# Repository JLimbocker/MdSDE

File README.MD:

###MdSDE###
This repository contains the Board files and Software for the SMU MdSDE Universal Biasing Board Project

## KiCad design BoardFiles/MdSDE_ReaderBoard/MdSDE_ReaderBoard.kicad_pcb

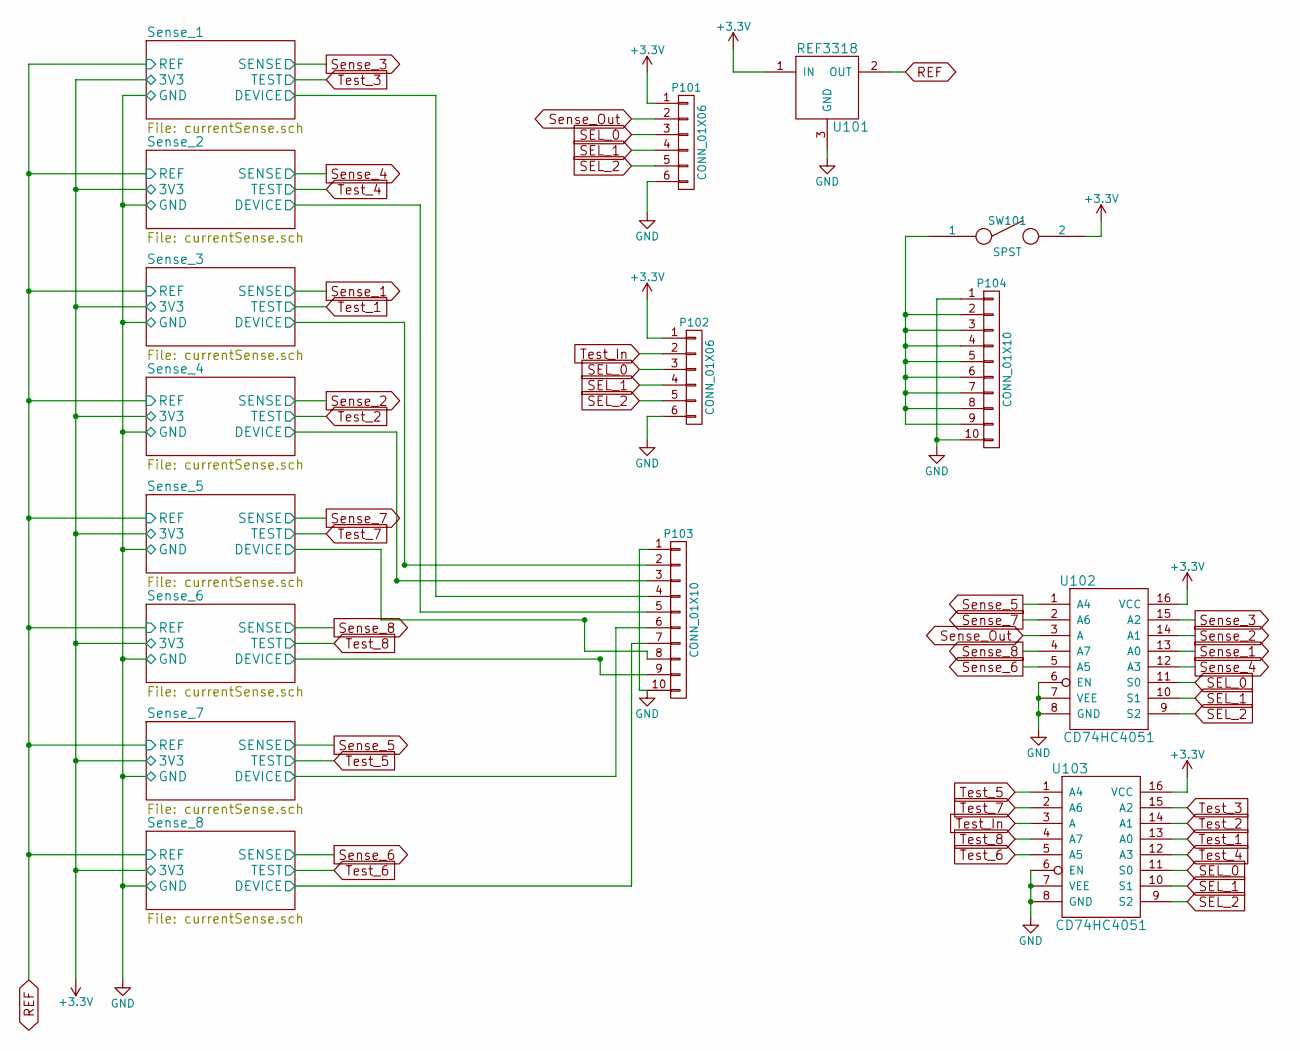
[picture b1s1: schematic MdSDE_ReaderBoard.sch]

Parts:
P101, P102: CONN_01X06; Pin_Header_Straight_1x06
P103, P104: CONN_01X10; Pin_Header_Straight_1x10
SW101: SPST; SW_DIP_x1_Slide
U101: REF3318; SOT-23_Handsoldering
U102, U103: CD74HC4051; SOIC-16_3.9x9.9mm_Pitch1.27mm

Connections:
+3V3: P101.1, P102.1, SW101.2, U101.1 (IN), U102.16 (VCC), U103.16 (VCC); also elsewhere on the board
/Sense_1/DEVICE: P103.4; also elsewhere on the board
/Sense_2/DEVICE: P103.5; also elsewhere on the board
/Sense_3/DEVICE: P103.2; also elsewhere on the board
/Sense_4/DEVICE: P103.3; also elsewhere on the board
/Sense_5/DEVICE: P103.8; also elsewhere on the board
/Sense_6/DEVICE: P103.9; also elsewhere on the board
/Sense_7/DEVICE: P103.6; also elsewhere on the board
/Sense_8/DEVICE: P103.7; also elsewhere on the board
GND: P101.6, P102.6, P103.1, P103.10, P104.1, P104.10, U101.3 (GND), U102.6 (EN), U102.7 (VEE), U102.8 (GND), U103.6 (EN), U103.7 (VEE), U103.8 (GND); also elsewhere on the board
unnamed: P104.2, P104.3, P104.4, P104.5, P104.6, P104.7, P104.8, P104.9, SW101.1
REF: U101.2 (OUT); also elsewhere on the board
SEL_0: P101.3, P102.3, U102.11 (S0), U103.11 (S0)
SEL_1: P101.4, P102.4, U102.10 (S1), U103.10 (S1)
SEL_2: P101.5, P102.5, U102.9 (S2), U103.9 (S2)
Sense_1: U102.13 (A0); also elsewhere on the board
Sense_2: U102.14 (A1); also elsewhere on the board
Sense_3: U102.15 (A2); also elsewhere on the board
Sense_4: U102.12 (A3); also elsewhere on the board
Sense_5: U102.1 (A4); also elsewhere on the board
Sense_6: U102.5 (A5); also elsewhere on the board
Sense_7: U102.2 (A6); also elsewhere on the board
Sense_8: U102.4 (A7); also elsewhere on the board
Sense_Out: P101.2, U102.3 (A)
Test_1: U103.13 (A0); also elsewhere on the board
Test_2: U103.14 (A1); also elsewhere on the board
Test_3: U103.15 (A2); also elsewhere on the board
Test_4: U103.12 (A3); also elsewhere on the board
Test_5: U103.1 (A4); also elsewhere on the board
Test_6: U103.5 (A5); also elsewhere on the board
Test_7: U103.2 (A6); also elsewhere on the board
Test_8: U103.4 (A7); also elsewhere on the board
Test_In: P102.2, U103.3 (A)

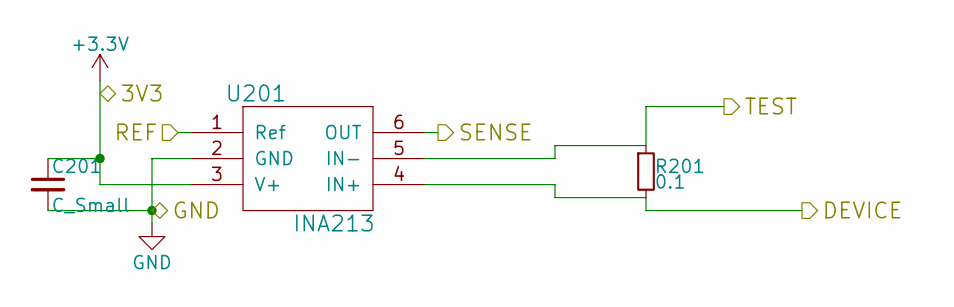
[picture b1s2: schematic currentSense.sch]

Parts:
C201: C_Small; C_1206_HandSoldering
R201: 0.1; R_1206_HandSoldering
U201: INA213; SC-70-6_Handsoldering

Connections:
+3V3: C201.1, U201.3 (V+); also elsewhere on the board
/Sense_3/DEVICE: R201.2, U201.4 (IN+); also elsewhere on the board
GND: C201.2, U201.2 (GND); also elsewhere on the board
REF: U201.1 (Ref); also elsewhere on the board
Sense_1: U201.6 (OUT); also elsewhere on the board
Test_1: R201.1, U201.5 (IN-); also elsewhere on the board

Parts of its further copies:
C301, C401, C501, C601, C701, C801, C901: C_Small; C_1206_HandSoldering
R301, R401, R501, R601, R701, R801, R901: 0.1; R_1206_HandSoldering
U301, U401, U501, U601, U701, U801, U901: INA213; SC-70-6_Handsoldering

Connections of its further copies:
+3V3: C301.1, C401.1, C501.1, C601.1, C701.1, C801.1, C901.1, U301.3 (V+), U401.3 (V+), U501.3 (V+), U601.3 (V+), U701.3 (V+), U801.3 (V+), U901.3 (V+); also elsewhere on the board
/Sense_1/DEVICE: R401.2, U401.4 (IN+); also elsewhere on the board
/Sense_2/DEVICE: R501.2, U501.4 (IN+); also elsewhere on the board
/Sense_4/DEVICE: R301.2, U301.4 (IN+); also elsewhere on the board
/Sense_5/DEVICE: R801.2, U801.4 (IN+); also elsewhere on the board
/Sense_6/DEVICE: R901.2, U901.4 (IN+); also elsewhere on the board
/Sense_7/DEVICE: R601.2, U601.4 (IN+); also elsewhere on the board
/Sense_8/DEVICE: R701.2, U701.4 (IN+); also elsewhere on the board
GND: C301.2, C401.2, C501.2, C601.2, C701.2, C801.2, C901.2, U301.2 (GND), U401.2 (GND), U501.2 (GND), U601.2 (GND), U701.2 (GND), U801.2 (GND), U901.2 (GND); also elsewhere on the board
REF: U301.1 (Ref), U401.1 (Ref), U501.1 (Ref), U601.1 (Ref), U701.1 (Ref), U801.1 (Ref), U901.1 (Ref); also elsewhere on the board
Sense_2: U301.6 (OUT); also elsewhere on the board
Sense_3: U401.6 (OUT); also elsewhere on the board
Sense_4: U501.6 (OUT); also elsewhere on the board
Sense_5: U601.6 (OUT); also elsewhere on the board
Sense_6: U701.6 (OUT); also elsewhere on the board
Sense_7: U801.6 (OUT); also elsewhere on the board
Sense_8: U901.6 (OUT); also elsewhere on the board
Test_2: R301.1, U301.5 (IN-); also elsewhere on the board
Test_3: R401.1, U401.5 (IN-); also elsewhere on the board
Test_4: R501.1, U501.5 (IN-); also elsewhere on the board
Test_5: R601.1, U601.5 (IN-); also elsewhere on the board
Test_6: R701.1, U701.5 (IN-); also elsewhere on the board
Test_7: R801.1, U801.5 (IN-); also elsewhere on the board
Test_8: R901.1, U901.5 (IN-); also elsewhere on the board

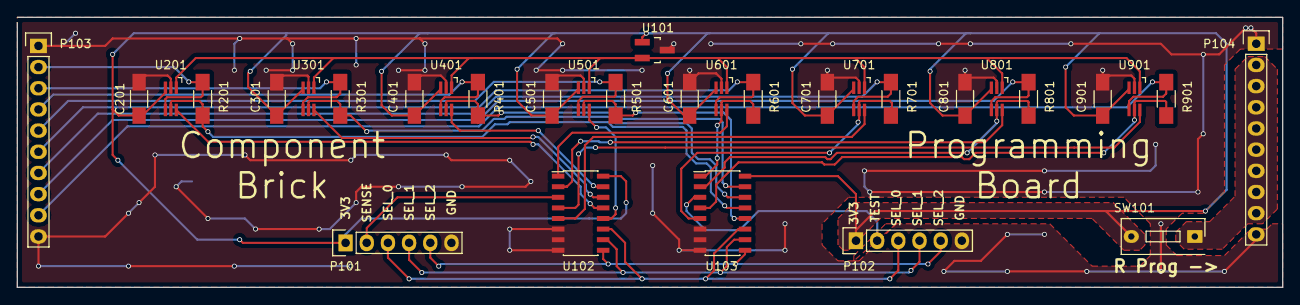
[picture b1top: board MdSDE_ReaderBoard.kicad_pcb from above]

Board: 2 copper layers, 151.8 x 32.4 mm, 32 parts (0 on the bottom side), 33 nets.

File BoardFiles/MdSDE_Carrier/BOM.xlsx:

ref | value5 | part | Quantity | Distributor | Dist Part # | MFR | MFR Part # | Price | Link
C | 10u | CP1_Small | 8 | Mouser | 140-REA470M1CBK0511P |  | REA470M1CBK-0511P | 0.06 | http://www.mouser.com/ProductDetail/Lelon/REA470M1CBK-0511P/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
C | 0.1u | C_Small | 16 | Mouser | 21RZ310-RC | Xicon | 21RZ310-RC | 0.08 | http://www.mouser.com/ProductDetail/Xicon/21RZ310-RC/?qs=sGA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
D | D | D | 16 | Mouser | 863-NSR0530HT1G | ON Semi | NSR0530HT1G | 0.14199999999999999 | http://www.mouser.com/ProductDetail/ON-Semiconductor/NSR0530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
P | 1x6 | CONN_01X06 | 8 | Mouser | 636-25630601RP2 | NorComp | 25630601RP2 | 1.83 | http://www.mouser.com/ProductDetail/NorComp/25630601RP2/?qs=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
P | 1x8 | CONN_01X08 | 4 | Mouser | 651-1789472 | Phoenix Contact | 1789472 | 8.48 | http://www.mouser.com/ProductDetail/Phoenix-Contact/1789472/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
P | 1x3 | CONN_01X03 | 1 | Mouser | 571-2828343 | TE Connectivity | 282834-3 | 1.51 | http://www.mouser.com/ProductDetail/TE-Connectivity/282834-3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
P | 2x7 | Socket_DIP14 | 16 | Mouser | 855-M22-7130742 | Harwin | M22-7130742 | 1.05 | http://www.mouser.com/ProductDetail/Harwin/M22-7130742/?qs=s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
R | 0.1 | R_Small | 16 | Mouser | 667-ERJ-8BWFR100V | Panasonic | ERJ-8BWFR100V | 1.17 | http://www.mouser.com/ProductDetail/Panasonic/ERJ-8BWFR100V/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
R | 2k | R_Small | 16 | Mouser | 660-RK73H2BTTD2001F | KOA Speer | RK73H2BTTD2001F | 0.1 | http://www.mouser.com/ProductDetail/KOA-Speer/RK73H2BTTD2001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
U | REF3318 | REF3318 | 8 | Mouser | 595-REF3318AIDBZT | TI | REF3318AIDBZT | 2.65 | http://www.mouser.com/search/ProductDetail.aspx?qs=7KoJEllG3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
U | INA213 | INA213 | 16 | Mouser | 595-INA213BIDCKR | TI | INA213BIDCKR | 1.46 | http://www.mouser.com/ProductDetail/Texas-Instruments/INA213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

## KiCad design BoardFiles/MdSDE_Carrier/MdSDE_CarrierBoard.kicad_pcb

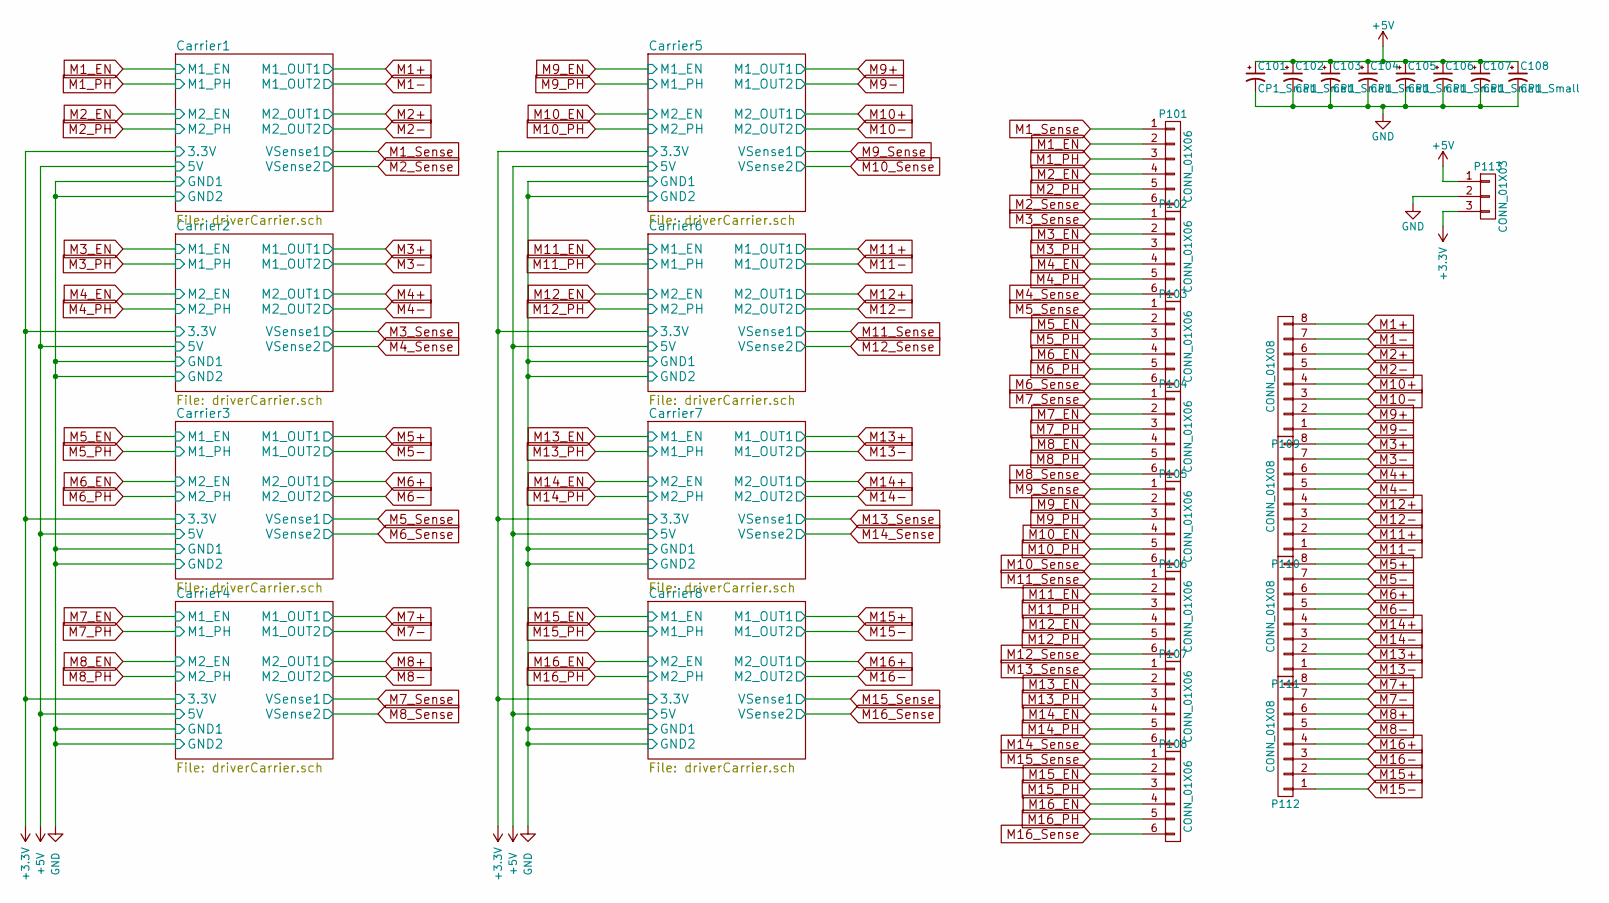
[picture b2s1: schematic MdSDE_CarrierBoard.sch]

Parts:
C101, C102, C103, C104, C105, C106, C107, C108: CP1_Small; C_Radial_D5_L6_P2.5
P101, P102, P103, P104, P105, P106, P107, P108: CONN_01X06; Pin_Header_Straight_1x06
P109, P110, P111, P112: CONN_01X08; Phoenix_FFKDS_V-25,4-8
P113: CONN_01X03; PINHEAD1-3

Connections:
+3V3: P113.3; also elsewhere on the board
+5V: C101.1, C102.1, C103.1, C104.1, C105.1, C106.1, C107.1, C108.1, P113.1; also elsewhere on the board
GND: C101.2, C102.2, C103.2, C104.2, C105.2, C106.2, C107.2, C108.2, P113.2; also elsewhere on the board
M1+: P109.8; also elsewhere on the board
M1-: P109.7; also elsewhere on the board
M1_EN: P101.2; also elsewhere on the board
M1_PH: P101.3; also elsewhere on the board
M1_Sense: P101.1; also elsewhere on the board
M2+: P109.6; also elsewhere on the board
M2-: P109.5; also elsewhere on the board
M2_EN: P101.4; also elsewhere on the board
M2_PH: P101.5; also elsewhere on the board
M2_Sense: P101.6; also elsewhere on the board
M3+: P110.8; also elsewhere on the board
M3-: P110.7; also elsewhere on the board
M3_EN: P102.2; also elsewhere on the board
M3_PH: P102.3; also elsewhere on the board
M3_Sense: P102.1; also elsewhere on the board
M4+: P110.6; also elsewhere on the board
M4-: P110.5; also elsewhere on the board
M4_EN: P102.4; also elsewhere on the board
M4_PH: P102.5; also elsewhere on the board
M4_Sense: P102.6; also elsewhere on the board
M5+: P111.8; also elsewhere on the board
M5-: P111.7; also elsewhere on the board
M5_EN: P103.2; also elsewhere on the board
M5_PH: P103.3; also elsewhere on the board
M5_Sense: P103.1; also elsewhere on the board
M6+: P111.6; also elsewhere on the board
M6-: P111.5; also elsewhere on the board
M6_EN: P103.4; also elsewhere on the board
M6_PH: P103.5; also elsewhere on the board
M6_Sense: P103.6; also elsewhere on the board
M7+: P112.8; also elsewhere on the board
M7-: P112.7; also elsewhere on the board
M7_EN: P104.2; also elsewhere on the board
M7_PH: P104.3; also elsewhere on the board
M7_Sense: P104.1; also elsewhere on the board
M8+: P112.6; also elsewhere on the board
M8-: P112.5; also elsewhere on the board
M8_EN: P104.4; also elsewhere on the board
M8_PH: P104.5; also elsewhere on the board
M8_Sense: P104.6; also elsewhere on the board
M9+: P109.2; also elsewhere on the board
M9-: P109.1; also elsewhere on the board
M9_EN: P105.2; also elsewhere on the board
M9_PH: P105.3; also elsewhere on the board
M9_Sense: P105.1; also elsewhere on the board
M10+: P109.4; also elsewhere on the board
M10-: P109.3; also elsewhere on the board
M10_EN: P105.4; also elsewhere on the board
M10_PH: P105.5; also elsewhere on the board
M10_Sense: P105.6; also elsewhere on the board
M11+: P110.2; also elsewhere on the board
M11-: P110.1; also elsewhere on the board
M11_EN: P106.2; also elsewhere on the board
M11_PH: P106.3; also elsewhere on the board
M11_Sense: P106.1; also elsewhere on the board
M12+: P110.4; also elsewhere on the board
M12-: P110.3; also elsewhere on the board
M12_EN: P106.4; also elsewhere on the board
M12_PH: P106.5; also elsewhere on the board
M12_Sense: P106.6; also elsewhere on the board
M13+: P111.2; also elsewhere on the board
M13-: P111.1; also elsewhere on the board
M13_EN: P107.2; also elsewhere on the board
M13_PH: P107.3; also elsewhere on the board
M13_Sense: P107.1; also elsewhere on the board
M14+: P111.4; also elsewhere on the board
M14-: P111.3; also elsewhere on the board
M14_EN: P107.4; also elsewhere on the board
M14_PH: P107.5; also elsewhere on the board
M14_Sense: P107.6; also elsewhere on the board
M15+: P112.2; also elsewhere on the board
M15-: P112.1; also elsewhere on the board
M15_EN: P108.2; also elsewhere on the board
M15_PH: P108.3; also elsewhere on the board
M15_Sense: P108.1; also elsewhere on the board
M16+: P112.4; also elsewhere on the board
M16-: P112.3; also elsewhere on the board
M16_EN: P108.4; also elsewhere on the board
M16_PH: P108.5; also elsewhere on the board
M16_Sense: P108.6; also elsewhere on the board

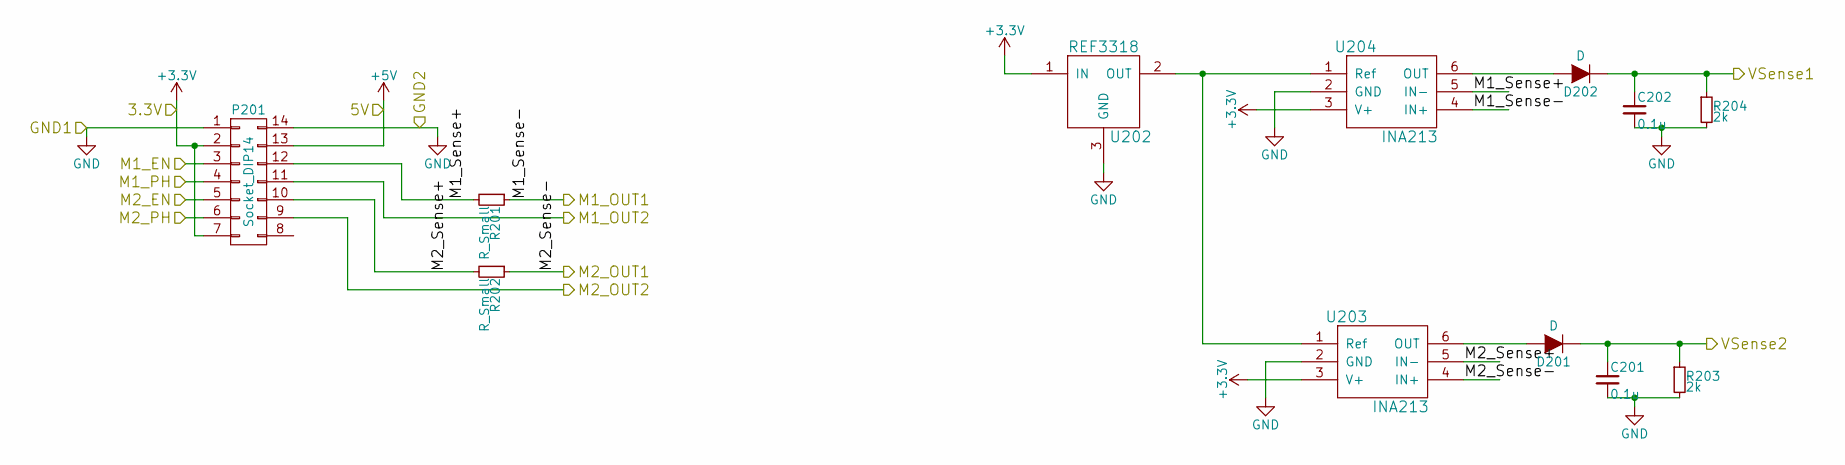
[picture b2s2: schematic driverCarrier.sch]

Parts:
C201, C202: 0.1u; C_Disc_D3_P2.5
D201, D202: D; SOD-323
P201: Socket_DIP14; DIP-14_W7.62mm
R201, R202: R_Small; R_1206_HandSoldering
R203, R204: 2k; R_1206_HandSoldering
U202: REF3318; SOT-23_Handsoldering
U203, U204: INA213; SC-70-6_Handsoldering

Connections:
+3V3: P201.2, P201.7, U202.1 (IN), U203.3 (V+), U204.3 (V+); also elsewhere on the board
+5V: P201.13; also elsewhere on the board
/Carrier1/M1_Sense+: P201.12, R201.2, U204.5 (IN-)
/Carrier1/M2_Sense+: P201.10, R202.2, U203.5 (IN-)
GND: C201.2, C202.2, P201.1, P201.14, R203.2, R204.2, U202.3 (GND), U203.2 (GND), U204.2 (GND); also elsewhere on the board
M1+: R201.1, U204.4 (IN+); also elsewhere on the board
M1-: P201.11; also elsewhere on the board
M1_EN: P201.3; also elsewhere on the board
M1_PH: P201.4; also elsewhere on the board
M1_Sense: C202.1, D202.1 (K), R204.1; also elsewhere on the board
M2+: R202.1, U203.4 (IN+); also elsewhere on the board
M2-: P201.9; also elsewhere on the board
M2_EN: P201.5; also elsewhere on the board
M2_PH: P201.6; also elsewhere on the board
M2_Sense: C201.1, D201.1 (K), R203.1; also elsewhere on the board
unnamed: D201.2 (A), U203.6 (OUT)
unnamed: D202.2 (A), U204.6 (OUT)
unnamed: U202.2 (OUT), U203.1 (Ref), U204.1 (Ref)

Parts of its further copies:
C301, C302, C401, C402, C501, C502, C601, C602, C701, C702, C801, C802, C901, C902: 0.1u; C_Disc_D3_P2.5
D301, D302, D401, D402, D501, D502, D601, D602, D701, D702, D801, D802, D901, D902: D; SOD-323
P301, P401, P501, P601, P701, P801, P901: Socket_DIP14; DIP-14_W7.62mm
R301, R302, R401, R402, R501, R502, R601, R602, R701, R702, R801, R802, R901, R902: R_Small; R_1206_HandSoldering
R303, R304, R403, R404, R503, R504, R603, R604, R703, R704, R803, R804, R903, R904: 2k; R_1206_HandSoldering
U302, U402, U502, U602, U702, U802, U902: REF3318; SOT-23_Handsoldering
U303, U304, U403, U404, U503, U504, U603, U604, U703, U704, U803, U804, U903, U904: INA213; SC-70-6_Handsoldering

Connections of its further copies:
+3V3: P301.2, P301.7, P401.2, P401.7, P501.2, P501.7, P601.2, P601.7, P701.2, P701.7, P801.2, P801.7, P901.2, P901.7, U302.1 (IN), U303.3 (V+), U304.3 (V+), U402.1 (IN), U403.3 (V+), U404.3 (V+), U502.1 (IN), U503.3 (V+), U504.3 (V+), U602.1 (IN), U603.3 (V+), U604.3 (V+), U702.1 (IN), U703.3 (V+), U704.3 (V+), U802.1 (IN), U803.3 (V+), U804.3 (V+), U902.1 (IN), U903.3 (V+), U904.3 (V+); also elsewhere on the board
+5V: P301.13, P401.13, P501.13, P601.13, P701.13, P801.13, P901.13; also elsewhere on the board
/Carrier2/M1_Sense+: P301.12, R301.2, U304.5 (IN-)
/Carrier2/M2_Sense+: P301.10, R302.2, U303.5 (IN-)
/Carrier3/M1_Sense+: P401.12, R401.2, U404.5 (IN-)
/Carrier3/M2_Sense+: P401.10, R402.2, U403.5 (IN-)
/Carrier4/M1_Sense+: P501.12, R501.2, U504.5 (IN-)
/Carrier4/M2_Sense+: P501.10, R502.2, U503.5 (IN-)
/Carrier5/M1_Sense+: P601.12, R601.2, U604.5 (IN-)
/Carrier5/M2_Sense+: P601.10, R602.2, U603.5 (IN-)
/Carrier6/M1_Sense+: P701.12, R701.2, U704.5 (IN-)
/Carrier6/M2_Sense+: P701.10, R702.2, U703.5 (IN-)
/Carrier7/M1_Sense+: P801.12, R801.2, U804.5 (IN-)
/Carrier7/M2_Sense+: P801.10, R802.2, U803.5 (IN-)
/Carrier8/M1_Sense+: P901.12, R901.2, U904.5 (IN-)
/Carrier8/M2_Sense+: P901.10, R902.2, U903.5 (IN-)
GND: C301.2, C302.2, C401.2, C402.2, C501.2, C502.2, C601.2, C602.2, C701.2, C702.2, C801.2, C802.2, C901.2, C902.2, P301.1, P301.14, P401.1, P401.14, P501.1, P501.14, P601.1, P601.14, P701.1, P701.14, P801.1, P801.14, P901.1, P901.14, R303.2, R304.2, R403.2, R404.2, R503.2, R504.2, R603.2, R604.2, R703.2, R704.2, R803.2, R804.2, R903.2, R904.2, U302.3 (GND), U303.2 (GND), U304.2 (GND), U402.3 (GND), U403.2 (GND), U404.2 (GND), U502.3 (GND), U503.2 (GND), U504.2 (GND), U602.3 (GND), U603.2 (GND), U604.2 (GND), U702.3 (GND), U703.2 (GND), U704.2 (GND), U802.3 (GND), U803.2 (GND), U804.2 (GND), U902.3 (GND), U903.2 (GND), U904.2 (GND); also elsewhere on the board
M3+: R301.1, U304.4 (IN+); also elsewhere on the board
M3-: P301.11; also elsewhere on the board
M3_EN: P301.3; also elsewhere on the board
M3_PH: P301.4; also elsewhere on the board
M3_Sense: C302.1, D302.1 (K), R304.1; also elsewhere on the board
M4+: R302.1, U303.4 (IN+); also elsewhere on the board
M4-: P301.9; also elsewhere on the board
M4_EN: P301.5; also elsewhere on the board
M4_PH: P301.6; also elsewhere on the board
M4_Sense: C301.1, D301.1 (K), R303.1; also elsewhere on the board
M5+: R401.1, U404.4 (IN+); also elsewhere on the board
M5-: P401.11; also elsewhere on the board
M5_EN: P401.3; also elsewhere on the board
M5_PH: P401.4; also elsewhere on the board
M5_Sense: C402.1, D402.1 (K), R404.1; also elsewhere on the board
M6+: R402.1, U403.4 (IN+); also elsewhere on the board
M6-: P401.9; also elsewhere on the board
M6_EN: P401.5; also elsewhere on the board
M6_PH: P401.6; also elsewhere on the board
M6_Sense: C401.1, D401.1 (K), R403.1; also elsewhere on the board
M7+: R501.1, U504.4 (IN+); also elsewhere on the board
M7-: P501.11; also elsewhere on the board
M7_EN: P501.3; also elsewhere on the board
M7_PH: P501.4; also elsewhere on the board
M7_Sense: C502.1, D502.1 (K), R504.1; also elsewhere on the board
M8+: R502.1, U503.4 (IN+); also elsewhere on the board
M8-: P501.9; also elsewhere on the board
M8_EN: P501.5; also elsewhere on the board
M8_PH: P501.6; also elsewhere on the board
M8_Sense: C501.1, D501.1 (K), R503.1; also elsewhere on the board
M9+: R601.1, U604.4 (IN+); also elsewhere on the board
M9-: P601.11; also elsewhere on the board
M9_EN: P601.3; also elsewhere on the board
M9_PH: P601.4; also elsewhere on the board
M9_Sense: C602.1, D602.1 (K), R604.1; also elsewhere on the board
M10+: R602.1, U603.4 (IN+); also elsewhere on the board
M10-: P601.9; also elsewhere on the board
M10_EN: P601.5; also elsewhere on the board
M10_PH: P601.6; also elsewhere on the board
M10_Sense: C601.1, D601.1 (K), R603.1; also elsewhere on the board
M11+: R701.1, U704.4 (IN+); also elsewhere on the board
M11-: P701.11; also elsewhere on the board
M11_EN: P701.3; also elsewhere on the board
M11_PH: P701.4; also elsewhere on the board
M11_Sense: C702.1, D702.1 (K), R704.1; also elsewhere on the board
M12+: R702.1, U703.4 (IN+); also elsewhere on the board
M12-: P701.9; also elsewhere on the board
M12_EN: P701.5; also elsewhere on the board
M12_PH: P701.6; also elsewhere on the board
M12_Sense: C701.1, D701.1 (K), R703.1; also elsewhere on the board
M13+: R801.1, U804.4 (IN+); also elsewhere on the board
M13-: P801.11; also elsewhere on the board
M13_EN: P801.3; also elsewhere on the board
M13_PH: P801.4; also elsewhere on the board
M13_Sense: C802.1, D802.1 (K), R804.1; also elsewhere on the board
M14+: R802.1, U803.4 (IN+); also elsewhere on the board
M14-: P801.9; also elsewhere on the board
M14_EN: P801.5; also elsewhere on the board
M14_PH: P801.6; also elsewhere on the board
M14_Sense: C801.1, D801.1 (K), R803.1; also elsewhere on the board
M15+: R901.1, U904.4 (IN+); also elsewhere on the board
M15-: P901.11; also elsewhere on the board
M15_EN: P901.3; also elsewhere on the board
M15_PH: P901.4; also elsewhere on the board
M15_Sense: C902.1, D902.1 (K), R904.1; also elsewhere on the board
M16+: R902.1, U903.4 (IN+); also elsewhere on the board
M16-: P901.9; also elsewhere on the board
M16_EN: P901.5; also elsewhere on the board
M16_PH: P901.6; also elsewhere on the board
M16_Sense: C901.1, D901.1 (K), R903.1; also elsewhere on the board
unnamed: D301.2 (A), U303.6 (OUT)
unnamed: D302.2 (A), U304.6 (OUT)
unnamed: D401.2 (A), U403.6 (OUT)
unnamed: D402.2 (A), U404.6 (OUT)
unnamed: D501.2 (A), U503.6 (OUT)
unnamed: D502.2 (A), U504.6 (OUT)
unnamed: D601.2 (A), U603.6 (OUT)
unnamed: D602.2 (A), U604.6 (OUT)
unnamed: D701.2 (A), U703.6 (OUT)
unnamed: D702.2 (A), U704.6 (OUT)
unnamed: D801.2 (A), U803.6 (OUT)
unnamed: D802.2 (A), U804.6 (OUT)
unnamed: D901.2 (A), U903.6 (OUT)
unnamed: D902.2 (A), U904.6 (OUT)
unnamed: U302.2 (OUT), U303.1 (Ref), U304.1 (Ref)
unnamed: U402.2 (OUT), U403.1 (Ref), U404.1 (Ref)
unnamed: U502.2 (OUT), U503.1 (Ref), U504.1 (Ref)
unnamed: U602.2 (OUT), U603.1 (Ref), U604.1 (Ref)
unnamed: U702.2 (OUT), U703.1 (Ref), U704.1 (Ref)
unnamed: U802.2 (OUT), U803.1 (Ref), U804.1 (Ref)
unnamed: U902.2 (OUT), U903.1 (Ref), U904.1 (Ref)

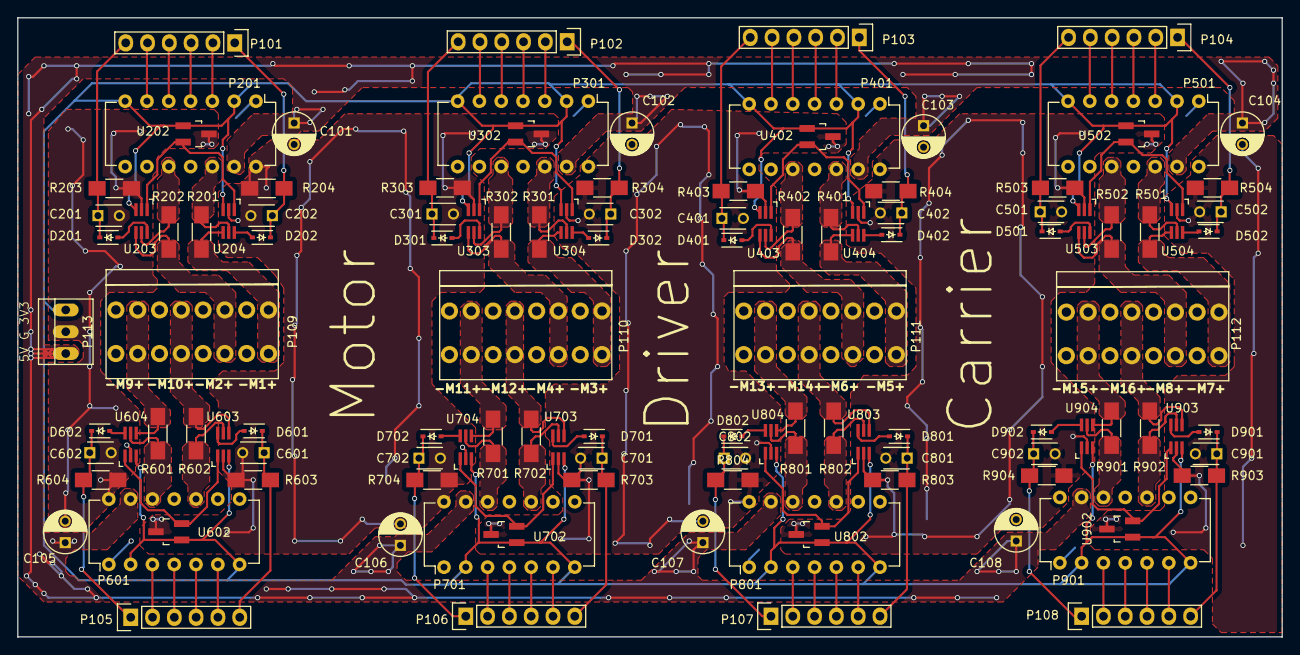
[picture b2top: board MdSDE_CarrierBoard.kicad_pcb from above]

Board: 2 copper layers, 147.3 x 72.1 mm, 117 parts (0 on the bottom side), 123 nets.

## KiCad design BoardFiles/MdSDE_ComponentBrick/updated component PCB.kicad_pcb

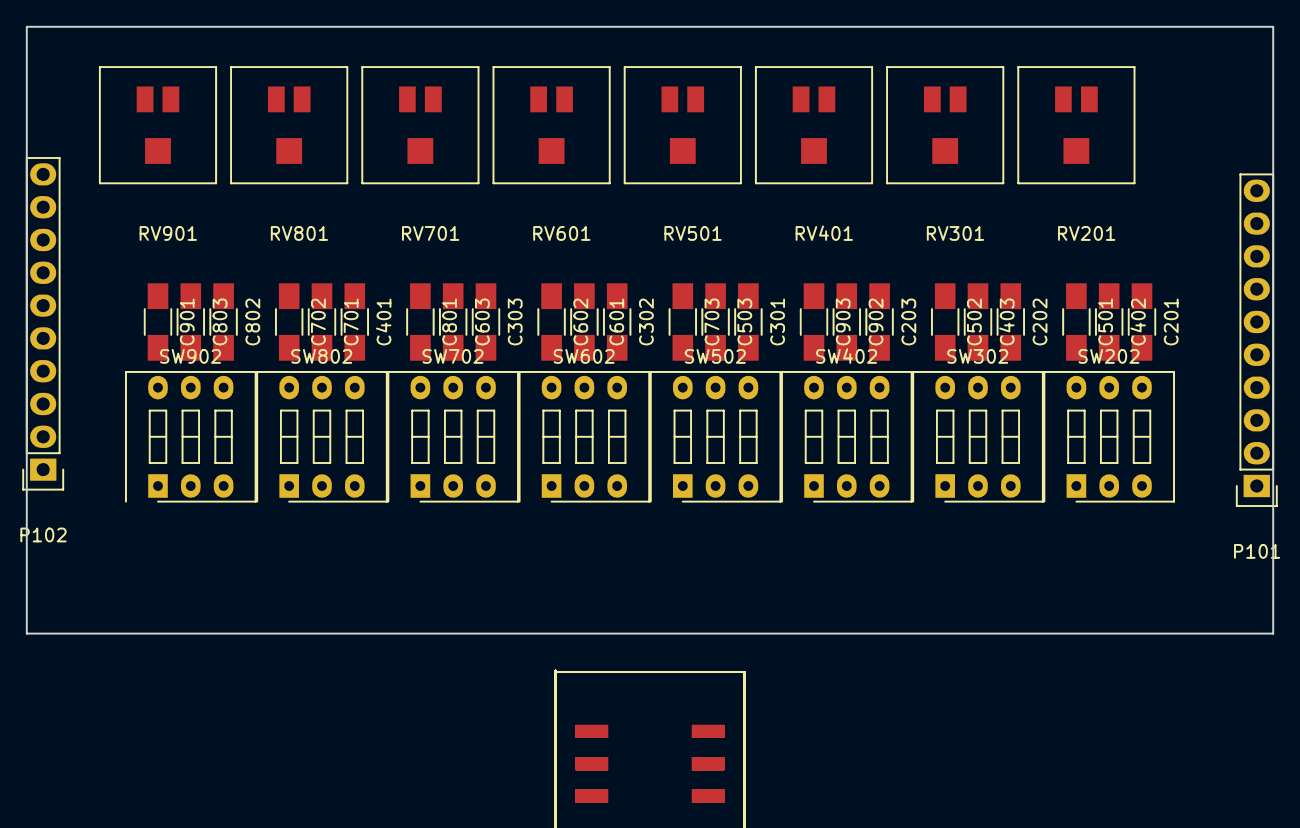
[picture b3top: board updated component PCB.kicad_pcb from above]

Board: 2 copper layers, 96.5 x 47.0 mm, 50 parts (0 on the bottom side), 57 nets, no tracks yet.

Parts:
C201, C202, C203, C301, C302, C303, C401, C402, C403, C501, C502, C503, C601, C602, C603, C701, C702, C703, C801, C802, C803, C901, C902, C903: C_Small; C_1206_HandSoldering
P101, P102: CONN_01X10; Pin_Header_Straight_1x10
RV201, RV301, RV401, RV501, RV601, RV701, RV801, RV901: POT; 3314_Potentiometer
SW201, SW301, SW401, SW501, SW601, SW701, SW801, SW901: Coded_Switch; SH-7000RotarySwitch
SW202, SW302, SW402, SW502, SW602, SW702, SW802, SW902: SPST_x3; SW_DIP_x3_Slide

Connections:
GND: C201.2, C202.2, C203.2, C301.2, C302.2, C303.2, C401.2, C402.2, C403.2, C501.2, C502.2, C503.2, C601.2, C602.2, C603.2, C701.2, C702.2, C703.2, C801.2, C802.2, C803.2, C901.2, C902.2, C903.2, P101.1, P101.10, P102.1, P102.10, SW201.5, SW202.4, SW301.5, SW302.4, SW401.5, SW402.4, SW501.5, SW502.4, SW601.5, SW602.4, SW701.5, SW702.4, SW801.5, SW802.4, SW901.5, SW902.4
unnamed: C201.1, SW201.4
unnamed: C202.1, SW201.3
unnamed: C203.1, SW201.2
unnamed: C301.1, SW301.4
unnamed: C302.1, SW301.3
unnamed: C303.1, SW301.2
unnamed: C401.1, SW401.4
unnamed: C402.1, SW401.3
unnamed: C403.1, SW401.2
unnamed: C501.1, SW501.4
unnamed: C502.1, SW501.3
unnamed: C503.1, SW501.2
unnamed: C601.1, SW601.4
unnamed: C602.1, SW601.3
unnamed: C603.1, SW601.2
unnamed: C701.1, SW701.4
unnamed: C702.1, SW701.3
unnamed: C703.1, SW701.2
unnamed: C801.1, SW801.4
unnamed: C802.1, SW801.3
unnamed: C803.1, SW801.2
unnamed: C901.1, SW901.4
unnamed: C902.1, SW901.3
unnamed: C903.1, SW901.2
unnamed: RV201.1, SW202.3
unnamed: RV201.2, SW202.2, SW202.5
unnamed: RV301.1, SW302.3
unnamed: RV301.2, SW302.2, SW302.5
unnamed: RV401.1, SW402.3
unnamed: RV401.2, SW402.2, SW402.5
unnamed: RV501.1, SW502.3
unnamed: RV501.2, SW502.2, SW502.5
unnamed: RV601.1, SW602.3
unnamed: RV601.2, SW602.2, SW602.5
unnamed: RV701.1, SW702.3
unnamed: RV701.2, SW702.2, SW702.5
unnamed: RV801.1, SW802.3
unnamed: RV801.2, SW802.2, SW802.5
unnamed: RV901.1, SW902.3
unnamed: RV901.2, SW902.2, SW902.5
Pin1: P101.2, SW201.1, SW202.1
Pin2: P101.3, SW301.1, SW302.1
Pin3: P101.4, SW501.1, SW502.1
Pin4: P101.5, SW401.1, SW402.1
Pin5: P101.6, SW601.1, SW602.1
Pin6: P101.7, SW701.1, SW702.1
Pin7: P101.8, SW901.1, SW902.1
Pin8: P101.9, SW801.1, SW802.1
Src1: P102.9, SW202.6
Src2: P102.8, SW302.6
Src3: P102.7, SW502.6
Src4: P102.6, SW402.6
Src5: P102.5, SW602.6
Src6: P102.4, SW702.6
Src7: P102.3, SW902.6
Src8: P102.2, SW802.6

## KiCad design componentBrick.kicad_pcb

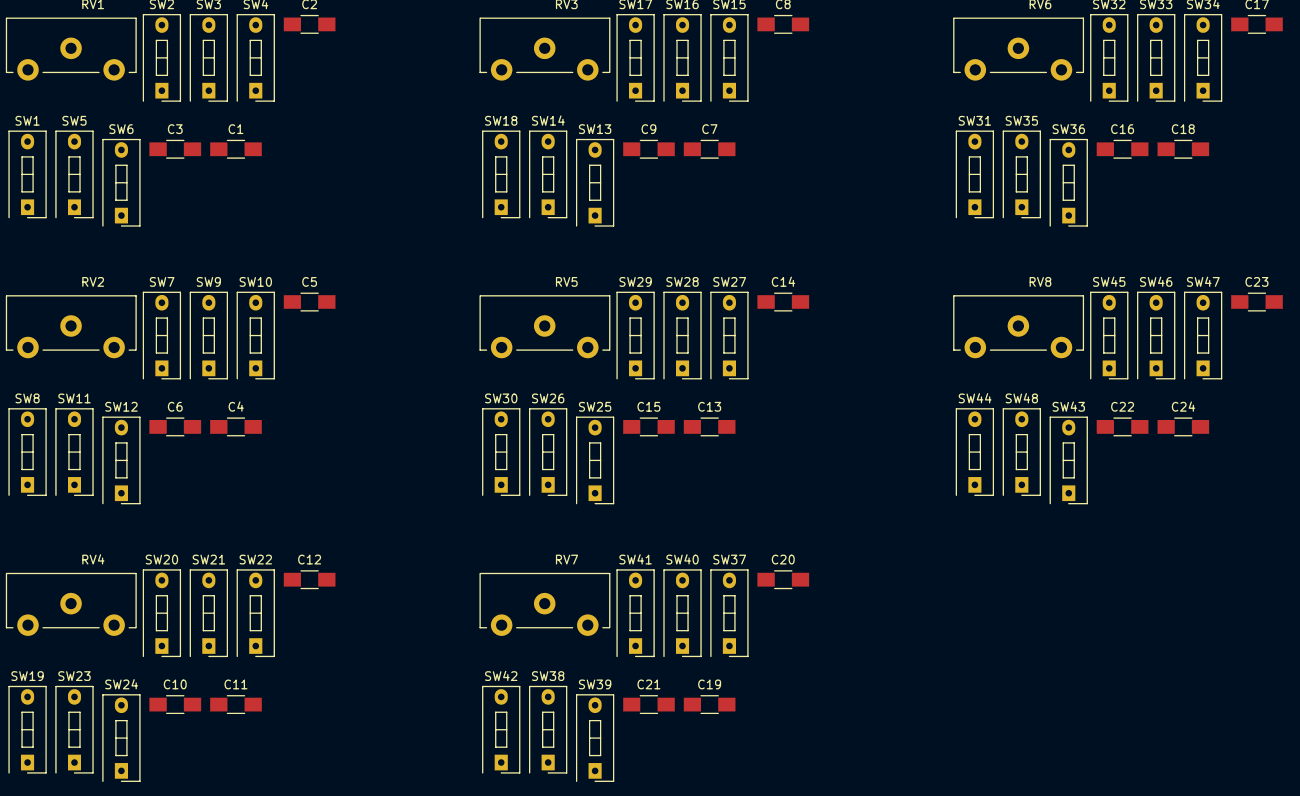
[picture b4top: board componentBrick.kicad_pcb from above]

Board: 2 copper layers, 80 parts (0 on the bottom side), 57 nets, no tracks yet.

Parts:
C1, C4, C7, C10, C13, C16, C19, C22: 10u; C_1206_HandSoldering
C2, C5, C8, C11, C14, C17, C20, C23: 1u; C_1206_HandSoldering
C3, C6, C9, C12, C15, C18, C21, C24: 0.1u; C_1206_HandSoldering
RV1, RV2, RV3, RV4, RV5, RV6, RV7, RV8: POT; Potentiometer_Trimmer-Piher-PT15-h2-5_vertical
SW1, SW2, SW3, SW4, SW5, SW6, SW7, SW8, SW9, SW10, SW11, SW12, SW13, SW14, SW15, SW16, SW17, SW18, SW19, SW20, SW21, SW22, SW23, SW24, SW25, SW26, SW27, SW28, SW29, SW30, SW31, SW32, SW33, SW34, SW35, SW36, SW37, SW38, SW39, SW40, SW41, SW42, SW43, SW44, SW45, SW46, SW47, SW48: SPST; SW_DIP_x1_Slide

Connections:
/devPin_1: SW1.1, SW2.1, SW3.1, SW4.1
/devPin_2: SW7.1, SW8.1, SW9.1, SW10.1
/devPin_3: SW13.1, SW14.1, SW15.1, SW16.1
/devPin_4: SW19.1, SW20.1, SW21.1, SW22.1
/devPin_5: SW25.1, SW26.1, SW27.1, SW28.1
/devPin_6: SW31.1, SW32.1, SW33.1, SW34.1
/devPin_7: SW37.1, SW38.1, SW39.1, SW40.1
/devPin_8: SW43.1, SW44.1, SW45.1, SW46.1
/srcPin_1: RV1.3, SW6.2
/srcPin_2: RV2.3, SW12.2
/srcPin_3: RV3.3, SW18.2
/srcPin_4: RV4.3, SW24.2
/srcPin_5: RV5.3, SW30.2
/srcPin_6: RV6.3, SW36.2
/srcPin_7: RV7.3, SW42.2
/srcPin_8: RV8.3, SW48.2
GND: C1.1, C2.1, C3.1, C4.1, C5.1, C6.1, C7.1, C8.1, C9.1, C10.1, C11.1, C12.1, C13.1, C14.1, C15.1, C16.1, C17.1, C18.1, C19.1, C20.1, C21.1, C22.1, C23.1, C24.1, SW5.2, SW11.2, SW17.2, SW23.2, SW29.2, SW35.2, SW41.2, SW47.2
unnamed: C1.2, SW1.2
unnamed: C2.2, SW2.2
unnamed: C3.2, SW3.2
unnamed: C4.2, SW7.2
unnamed: C5.2, SW8.2
unnamed: C6.2, SW9.2
unnamed: C7.2, SW13.2
unnamed: C8.2, SW14.2
unnamed: C9.2, SW15.2
unnamed: C10.2, SW19.2
unnamed: C11.2, SW20.2
unnamed: C12.2, SW21.2
unnamed: C13.2, SW25.2
unnamed: C14.2, SW26.2
unnamed: C15.2, SW27.2
unnamed: C16.2, SW31.2
unnamed: C17.2, SW32.2
unnamed: C18.2, SW33.2
unnamed: C19.2, SW37.2
unnamed: C20.2, SW38.2
unnamed: C21.2, SW39.2
unnamed: C22.2, SW43.2
unnamed: C23.2, SW44.2
unnamed: C24.2, SW45.2
unnamed: RV1.1, SW5.1
unnamed: RV1.2, SW4.2, SW6.1
unnamed: RV2.1, SW11.1
unnamed: RV2.2, SW10.2, SW12.1
unnamed: RV3.1, SW17.1
unnamed: RV3.2, SW16.2, SW18.1
unnamed: RV4.1, SW23.1
unnamed: RV4.2, SW22.2, SW24.1
unnamed: RV5.1, SW29.1
unnamed: RV5.2, SW28.2, SW30.1
unnamed: RV6.1, SW35.1
unnamed: RV6.2, SW34.2, SW36.1
unnamed: RV7.1, SW41.1
unnamed: RV7.2, SW40.2, SW42.1
unnamed: RV8.1, SW47.1
unnamed: RV8.2, SW46.2, SW48.1

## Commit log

2016-02-16 Changed Structure
2016-02-16 Removed Duplicates
2016-02-16 Added directories
2016-02-29 Added files via upload
2016-03-01 Created ComponentBrick.pro
    Created Component Brick Project. Added component library for MdSDE,
    included relative search path, included library.
    Added schematic component for DIP Switches “SPST_x3”
2016-03-03 Footprints
    These are the footprints for the potentiometer and the rotary switch.
2016-03-03 Updated Outlines
    The initial files had incorrect outlines. This fixes that issue.
2016-03-04 updated component pcb
    updated the component pcb
2016-03-14 Added Separate Projects for boards
    Added Component Brick Project
    Added Test Board Project
2016-03-15 Updated footprints
    Reduced size of bounding rectangle on components
2016-03-15 Updated footprints
    footprints updated
2016-03-15 Merge remote-tracking branch 'origin/master'
    # Conflicts:
    # BoardFiles/MdSDE_ComponentBrick/MdSDE_ComponentBrick.net
2016-03-15 correct spacing for pcb
    pre-traced component pcb with correct dimensions
2016-03-16 Checked layout, placed three caps
2016-03-16 updated layout
    updated layout without traces
2016-03-16 updated pcb routing traces
    began the process of routing traces
2016-03-16 updated traces
    more work on the tracks
2016-03-16 updated traces
    more updates to the tracks
2016-03-17 Finished PCB Layout for component brick
2016-03-21 Built motor driver carrier
2016-03-22 Added Reader Board
